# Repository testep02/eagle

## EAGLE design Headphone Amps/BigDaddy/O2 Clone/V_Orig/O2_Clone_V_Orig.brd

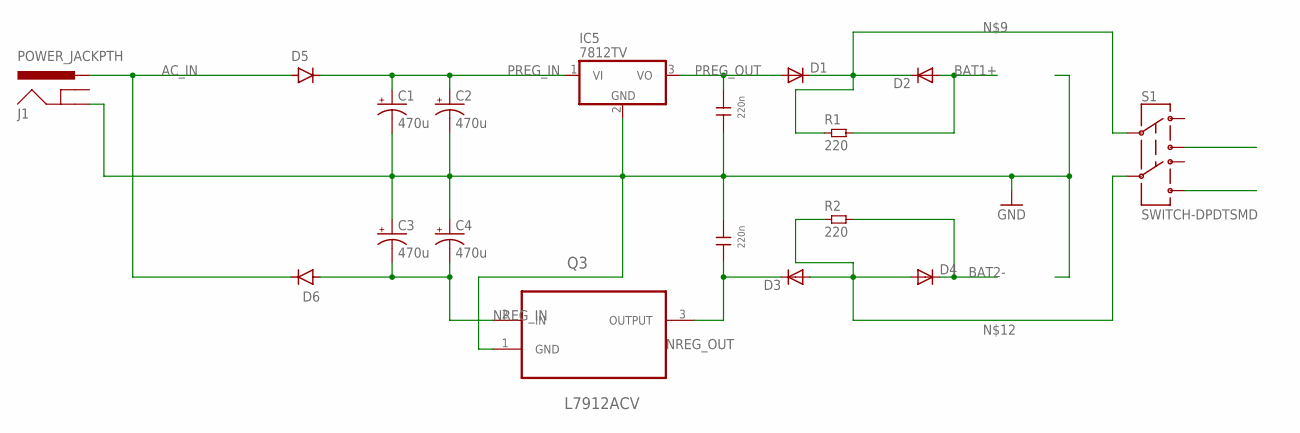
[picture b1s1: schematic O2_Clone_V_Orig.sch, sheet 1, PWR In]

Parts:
C1, C2, C3, C4: 470u; E5-10,5
C5, C6: 220n; 3,0X7,5RM5,0
D1, D2, D3, D4: DIODE-SMB; SMB
D5, D6: DIODE-SMX; SMX
IC5: 7812TV; TO220V
J1: POWER_JACKPTH; POWER_JACK_PTH
Q3: L7912ACV; TO254P450X1020X1935-3P
R1, R2: 220; 0603L3
S1: SWITCH-DPDTSMD; AYZ0202

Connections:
AC_IN: D5.1 (ANODE), D6.2 (CATHODE), J1.PWR
BAT1+: D2.A, R1.P$2 (2)
BAT2-: D4.C, R2.P$2 (2)
GND: C1.-, C2.-, C3.+, C4.+, C5.1, C6.2, IC5.2 (GND), J1.GND, Q3.1 (GND); also elsewhere on the board
unnamed: D1.C, D2.C, R1.P$1 (1), S1.2
unnamed: D3.A, D4.A, R2.P$1 (1), S1.5
NEG_OUT: S1.6
NREG_IN: C3.-, C4.-, D6.1 (ANODE), Q3.2 (IN)
NREG_OUT: C6.1, D3.C, Q3.3 (OUTPUT)
POS_OUT: S1.3
PREG_IN: C1.+, C2.+, D5.2 (CATHODE), IC5.1 (VI)
PREG_OUT: C5.2, D1.A, IC5.3 (VO)

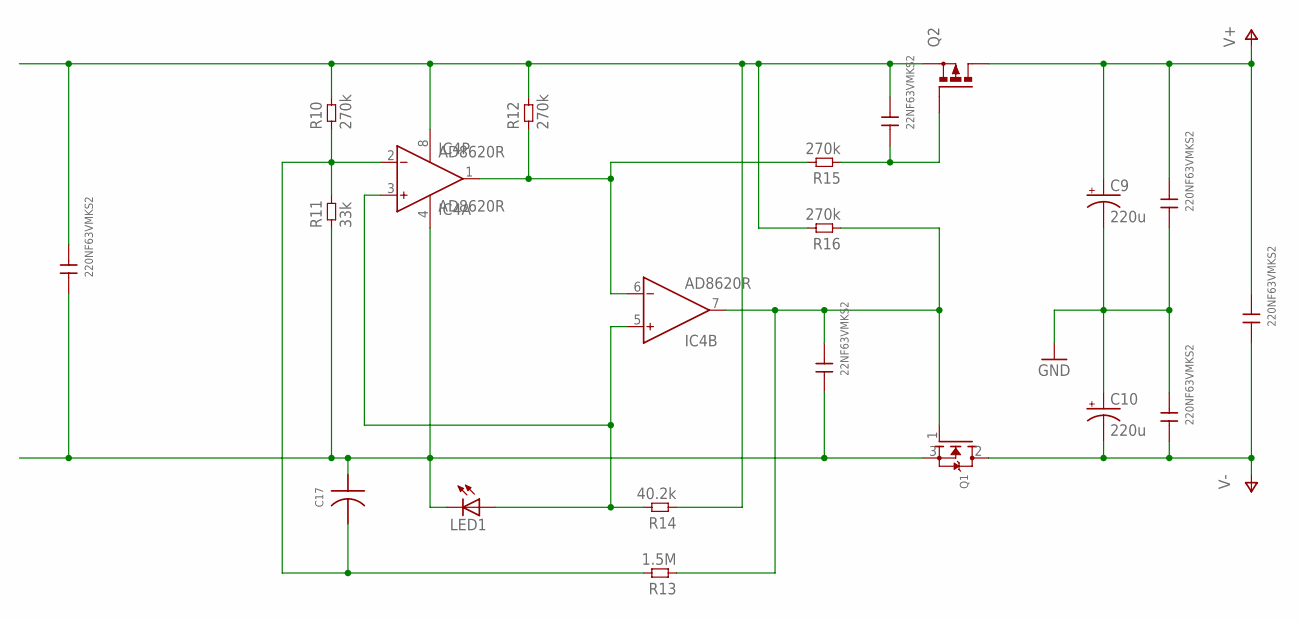
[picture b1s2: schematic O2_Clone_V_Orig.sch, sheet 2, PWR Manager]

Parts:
C7, C8: 22NF63VMKS2; 2,5X6,5RM5,0
C9, C10: 220u; E3,5-8
C11, C12, C13, C14: 220NF63VMKS2; 3,0X7,5RM5,0
C17: PCAP0805LEVEL3; R0805
IC4: AD8620R; SO8
LED1: LED3MM
Q1: MOSFET-NGDS_TO220V; TO220V
Q2: PMOSFET_PTO220BV; TO220BV
R10, R12, R15, R16: 270k; 0603L3
R11: 33k; 0603L3
R13: 1.5M; 0603L3
R14: 40.2k; 0603L3

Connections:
GND: C9.-, C10.+, C11.1, C12.2; also elsewhere on the board
unnamed: IC4.1 (OUT), IC4.6 (IN-), R12.P$1 (1), R15.P$2 (2)
unnamed: IC4.3 (IN+), IC4.5 (IN+), LED1.A, R14.P$2 (2)
unnamed: C8.1, C14.1, C17.P$2, IC4.4 (V-), LED1.K (C), Q1.3 (S), R11.P$1 (1)
unnamed: C17.P$1, IC4.2 (IN-), R10.P$1 (1), R11.P$2 (2), R13.P$2 (2)
unnamed: C7.2, C14.2, IC4.8 (V+), Q2.S, R10.P$2 (2), R12.P$2 (2), R14.P$1 (1), R16.P$2 (2)
unnamed: C7.1, Q2.G, R15.P$1 (1)
unnamed: C8.2, IC4.7 (OUT), Q1.1 (G), R13.P$1 (1), R16.P$1 (1)
V+: C9.+, C11.2, C13.2, Q2.D; also elsewhere on the board
V-: C10.-, C12.1, C13.1, Q1.2 (D); also elsewhere on the board

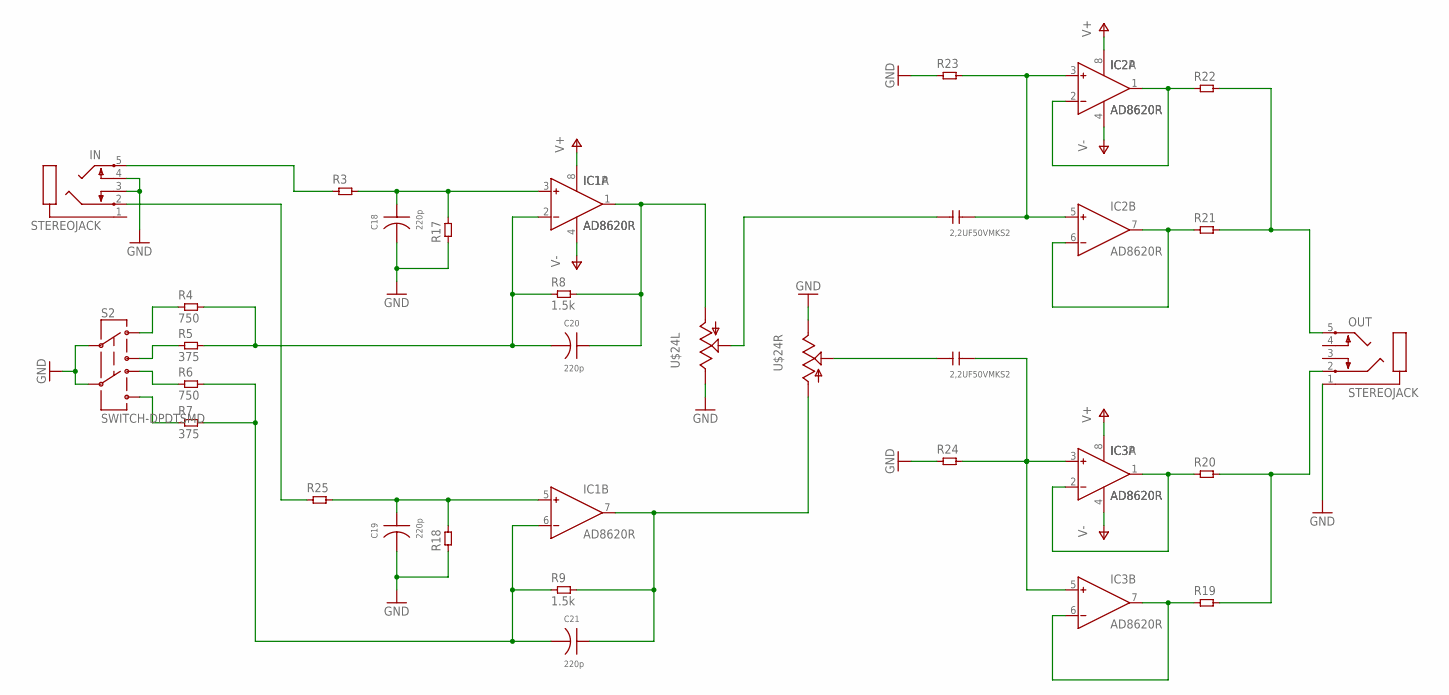
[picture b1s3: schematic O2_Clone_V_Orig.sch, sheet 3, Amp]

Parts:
C15, C16: 2,2UF50VMKS2; 7,2X13,0RM5,0
C18, C19, C20, C21: 220p; R0603
IC1, IC2, IC3: AD8620R; SO8
IN: STEREOJACK; STX3100
OUT: STEREOJACK; STX3100
R3, R17, R18, R19, R20, R21, R22, R23, R24, R25: RES0603L3; 0603L3
R4, R6: 750; 0603L3
R5, R7: 375; 0603L3
R8, R9: 1.5k; 0603L3
S2: SWITCH-DPDTSMD; AYZ0202
U$24: ALPS_RK0971221Z0N; ALPS_RK0971221Z0X

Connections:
GND: C18.P$1, C19.P$1, IN.3, IN.4, OUT.1, R17.P$1 (1), R18.P$1 (1), R23.P$1 (1), R24.P$1 (1), S2.2, S2.5, U$24.I1 (3), U$24.I2 (3); also elsewhere on the board
unnamed: IC2.1 (OUT), IC2.2 (IN-), R22.P$1 (1)
unnamed: IC2.6 (IN-), IC2.7 (OUT), R21.P$1 (1)
unnamed: IC3.1 (OUT), IC3.2 (IN-), R20.P$1 (1)
unnamed: IC3.6 (IN-), IC3.7 (OUT), R19.P$1 (1)
unnamed: OUT.5, R21.P$2 (2), R22.P$2 (2)
unnamed: OUT.2, R19.P$2 (2), R20.P$2 (2)
unnamed: C16.2, IC2.3 (IN+), IC2.5 (IN+), R23.P$2 (2)
unnamed: C15.2, IC3.3 (IN+), IC3.5 (IN+), R24.P$2 (2)
unnamed: C20.P$2, IC1.1 (OUT), R8.P$2 (2), U$24.G1 (1)
unnamed: C20.P$1, IC1.2 (IN-), R4.P$2 (2), R5.P$2 (2), R8.P$1 (1)
unnamed: C21.P$2, IC1.7 (OUT), R9.P$2 (2), U$24.G2 (1)
unnamed: C15.1, U$24.O2 (2)
unnamed: C18.P$2, IC1.3 (IN+), R3.P$2 (2), R17.P$2 (2)
unnamed: C19.P$2, IC1.5 (IN+), R18.P$2 (2), R25.P$2 (2)
unnamed: IN.5, R3.P$1 (1)
unnamed: IN.2, R25.P$1 (1)
unnamed: R5.P$1 (1), S2.3
unnamed: R6.P$1 (1), S2.4
unnamed: R4.P$1 (1), S2.1
unnamed: R7.P$1 (1), S2.6
unnamed: C21.P$1, IC1.6 (IN-), R6.P$2 (2), R7.P$2 (2), R9.P$1 (1)
unnamed: C16.1, U$24.O1 (2)
S1: U$24.S1
S2: U$24.S2
V+: IC1.8 (V+), IC2.8 (V+), IC3.8 (V+); also elsewhere on the board
V-: IC1.4 (V-), IC2.4 (V-), IC3.4 (V-); also elsewhere on the board

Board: 2 copper layers, 67 parts (0 on the bottom side), 41 nets, no tracks yet.

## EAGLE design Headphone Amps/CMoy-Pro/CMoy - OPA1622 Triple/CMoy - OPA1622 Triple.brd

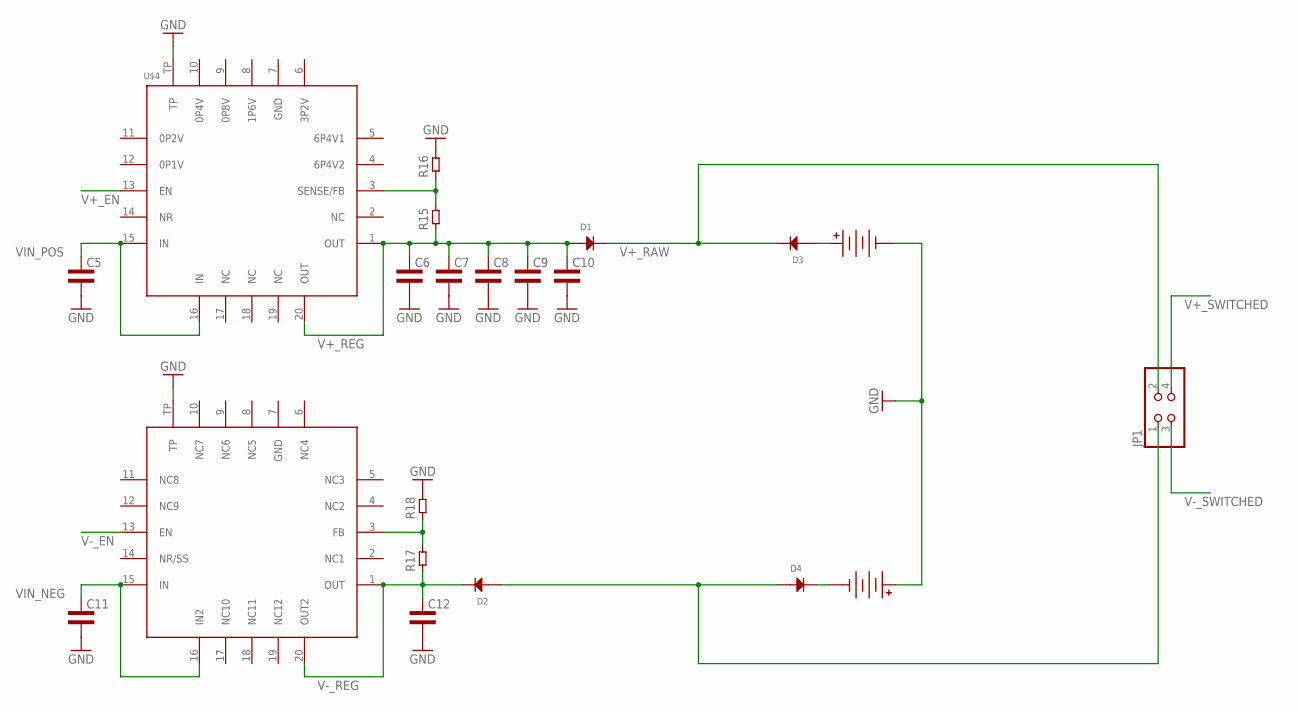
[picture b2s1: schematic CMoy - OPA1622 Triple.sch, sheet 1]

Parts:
BATT1, BATT2: BATT_9V; 9V_FEMALE
C5, C6, C7, C8, C9, C10, C11, C12: CAP0805L3; 0805L3
D1, D2, D3, D4: DIODEMINI2-F3-B; MINI2-F3-B
JP1: PINHD-2X2; 2X02
R15, R16, R17, R18: RES0603L3; 0603L3
U$4: POWER-SUPPLY_POS_V1_TI_LDO_TPS7A4700; POWER-SUPPLY_POS_V1_TI_LDO_VQFN-20
U$5: POWER-SUPPLY_POS_V1_TI_LDO_TPS7A3301RGWT; POWER-SUPPLY_POS_V1_TI_LDO_VQFN-20

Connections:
GND: BATT1.N1 (NEG), BATT1.N2 (NEG), BATT1.N3 (NEG), BATT2.P1 (POS), BATT2.P2 (POS), BATT2.P3 (POS), C5.2, C6.2, C7.2, C8.2, C9.2, C10.2, C11.2, C12.2, R16.P$2 (2), R18.P$2 (2), U$4.TP, U$5.TP; also elsewhere on the board
unnamed: BATT1.P1 (POS), BATT1.P2 (POS), BATT1.P3 (POS), D3.2 (ANODE)
unnamed: BATT2.N1 (NEG), BATT2.N2 (NEG), BATT2.N3 (NEG), D4.1 (CATHODE)
V+_EN: U$4.13 (EN)
V+_FB: R15.P$2 (2), R16.P$1 (1), U$4.3 (SENSE/FB)
V+_RAW: D1.1 (CATHODE), D3.1 (CATHODE), JP1.2
V+_REG: C6.1, C7.1, C8.1, C9.1, C10.1, D1.2 (ANODE), R15.P$1 (1), U$4.1 (OUT), U$4.20 (OUT)
V+_SWITCHED: JP1.4; also elsewhere on the board
V-_EN: U$5.13 (EN)
V-_FB: R17.P$2 (2), R18.P$1 (1), U$5.3 (FB)
V-_RAW: D2.2 (ANODE), D4.2 (ANODE), JP1.1
V-_REG: C12.1, D2.1 (CATHODE), R17.P$1 (1), U$5.1 (OUT), U$5.20 (OUT2)
V-_SWITCHED: JP1.3; also elsewhere on the board
VIN_NEG: C11.1, U$5.15 (IN), U$5.16 (IN2)
VIN_POS: C5.1, U$4.15 (IN), U$4.16 (IN)

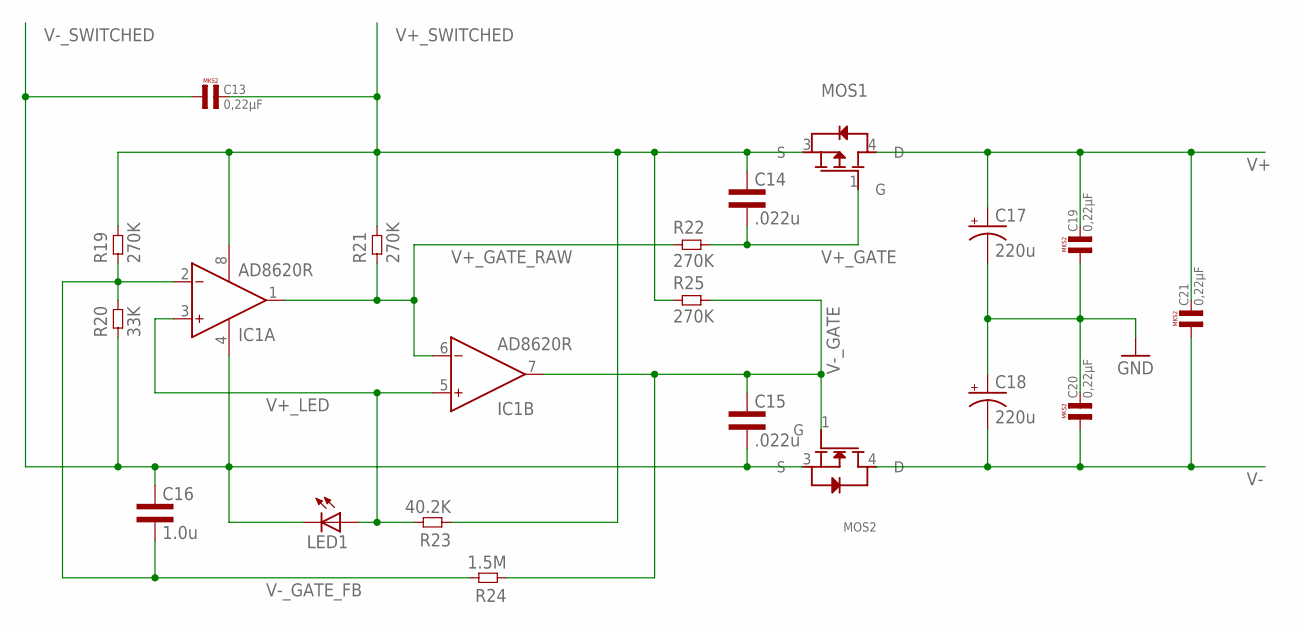
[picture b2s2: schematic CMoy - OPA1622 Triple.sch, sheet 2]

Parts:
C13, C19, C20, C21: 0,22µF; R5B3
C14, C15: .022u; 0603L3
C16: 1.0u; 0603L3
C17, C18: 220u; E3,5-8
IC1: AD8620R; SO8
LED1: LED3MM
MOS1: MOSFET-P; DPAK-3
MOS2: MOSFET-N; DPAK-3
R19, R21, R22, R25: 270K; 0603L3
R20: 33K; 0603L3
R23: 40.2K; 0603L3
R24: 1.5M; 0603L3

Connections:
GND: C17.-, C18.+, C19.1, C20.2; also elsewhere on the board
V+: C17.+, C19.2, C21.2, MOS1.4 (D); also elsewhere on the board
V+_GATE: C14.P$2 (2), MOS1.1 (G), R22.P$2 (2)
V+_GATE_RAW: IC1.1 (OUT), IC1.6 (IN-), R21.P$1 (1), R22.P$1 (1)
V+_LED: IC1.3 (IN+), IC1.5 (IN+), LED1.A, R23.P$2 (2)
V+_SWITCHED: C13.2, C14.P$1 (1), IC1.8 (V+), MOS1.3 (S), R19.P$2 (2), R21.P$2 (2), R23.P$1 (1), R25.P$1 (1); also elsewhere on the board
V-: C18.-, C20.1, C21.1, MOS2.4 (D); also elsewhere on the board
V-_GATE: C15.P$1 (1), IC1.7 (OUT), MOS2.1 (G), R24.P$1 (1), R25.P$2 (2)
V-_GATE_FB: C16.P$2 (2), IC1.2 (IN-), R19.P$1 (1), R20.P$2 (2), R24.P$2 (2)
V-_SWITCHED: C13.1, C15.P$2 (2), C16.P$1 (1), IC1.4 (V-), LED1.K (C), MOS2.3 (S), R20.P$1 (1); also elsewhere on the board

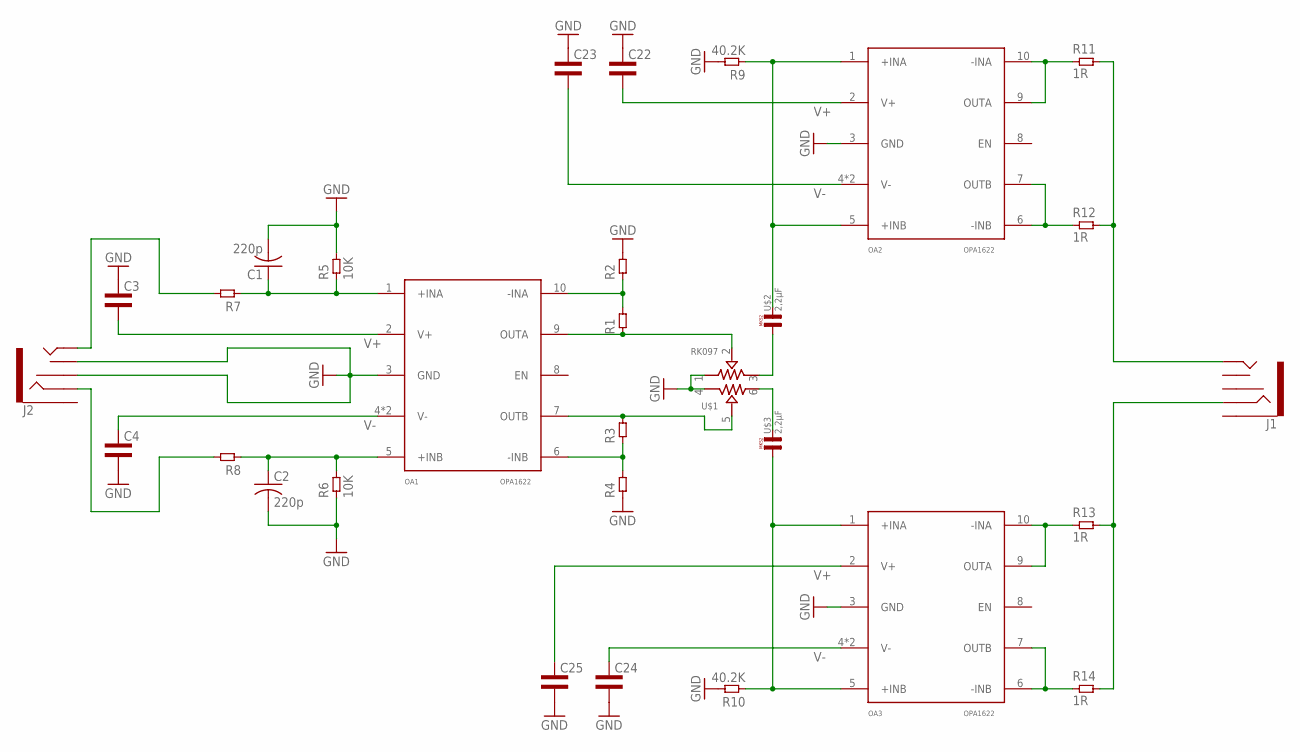
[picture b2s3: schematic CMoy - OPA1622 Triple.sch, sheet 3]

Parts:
C1, C2: 220p; C025-050X050
C3, C4, C22, C23, C24, C25: CAP0603L3; 0603L3
J1, J2: AUDIO-JACK2SMD; AUDIO-JACK-3.5MM-SMD
OA1, OA2, OA3: OPA1622; S-PVSON-N10
R1, R2, R3, R4, R7, R8: RES0603L3; 0603L3
R5, R6: 10K; 0603L3
R9, R10: 40.2K; 0603L3
R11, R12, R13, R14: 1R; 0805L3
U$1: RK097
U$2, U$3: 2,2µF; R5B7K2

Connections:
GND: C1.2, C2.2, C3.P$1 (1), C4.P$2 (2), C22.P$1 (1), C23.P$1 (1), C24.P$2 (2), C25.P$2 (2), J2.RSH, J2.TSH, OA1.3 (GND), OA2.3 (GND), OA3.3 (GND), R2.P$2 (2), R4.P$1 (1), R5.P$2 (2), R6.P$1 (1), R9.P$2 (2), R10.P$2 (2), U$1.1, U$1.4; also elsewhere on the board
unnamed: C1.1, OA1.1 (+INA), R5.P$1 (1), R7.P$1 (1)
unnamed: C2.1, OA1.5 (+INB), R6.P$2 (2), R8.P$1 (1)
unnamed: OA1.10 (-INA), R1.P$2 (2), R2.P$1 (1)
unnamed: OA1.6 (-INB), R3.P$1 (1), R4.P$2 (2)
unnamed: OA1.9 (OUTA), R1.P$1 (1), U$1.2
unnamed: OA1.7 (OUTB), R3.P$2 (2), U$1.5
unnamed: U$1.3, U$2.1
unnamed: J2.TIP, R7.P$2 (2)
unnamed: J2.RING, R8.P$2 (2)
unnamed: U$1.6, U$3.2
unnamed: OA2.1 (+INA), OA2.5 (+INB), R9.P$1 (1), U$2.2
unnamed: OA3.1 (+INA), OA3.5 (+INB), R10.P$1 (1), U$3.1
unnamed: OA2.9 (OUTA), OA2.10 (-INA), R11.1
unnamed: OA3.9 (OUTA), OA3.10 (-INA), R13.1
unnamed: OA3.6 (-INB), OA3.7 (OUTB), R14.1
unnamed: OA2.6 (-INB), OA2.7 (OUTB), R12.1
unnamed: J1.TIP, R11.2, R12.2
unnamed: J1.RING, R13.2, R14.2
V+: C3.P$2 (2), C22.P$2 (2), C25.P$1 (1), OA1.2 (V+), OA2.2 (V+), OA3.2 (V+); also elsewhere on the board
V-: C4.P$1 (1), C23.P$2 (2), C24.P$1 (1), OA1.4 (V-), OA1.TP (V-), OA2.4 (V-), OA2.TP (V-), OA3.4 (V-), OA3.TP (V-); also elsewhere on the board

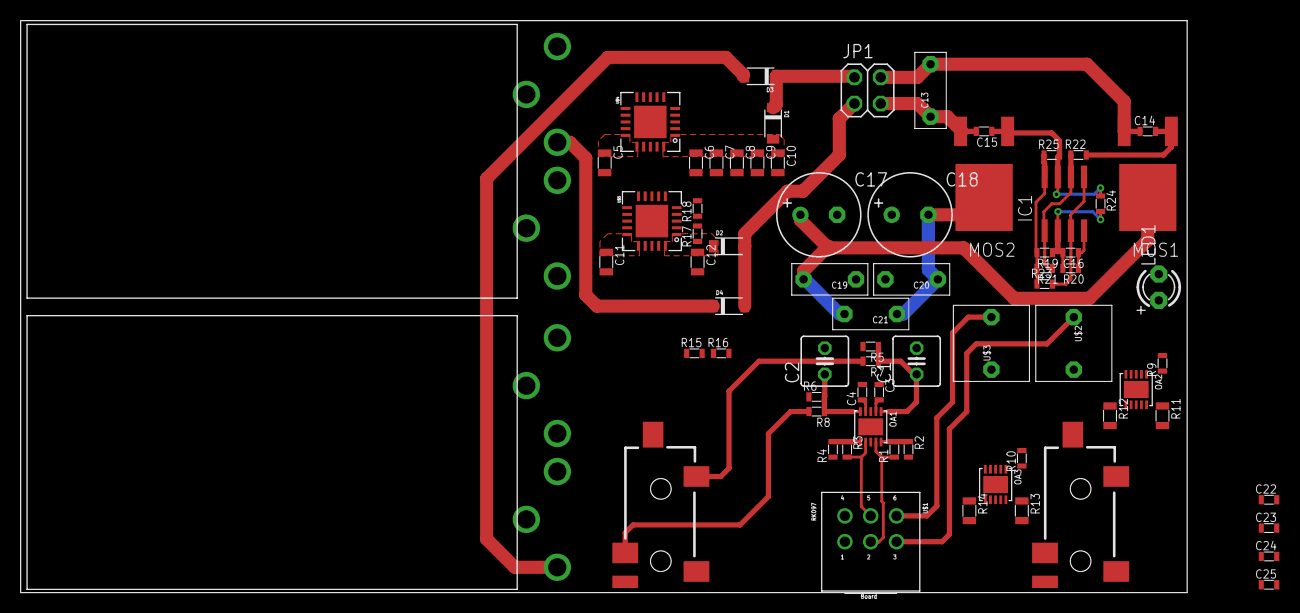
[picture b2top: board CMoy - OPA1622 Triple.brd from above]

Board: 2 copper layers, 112.9 x 55.4 mm, 71 parts (0 on the bottom side), 38 nets.

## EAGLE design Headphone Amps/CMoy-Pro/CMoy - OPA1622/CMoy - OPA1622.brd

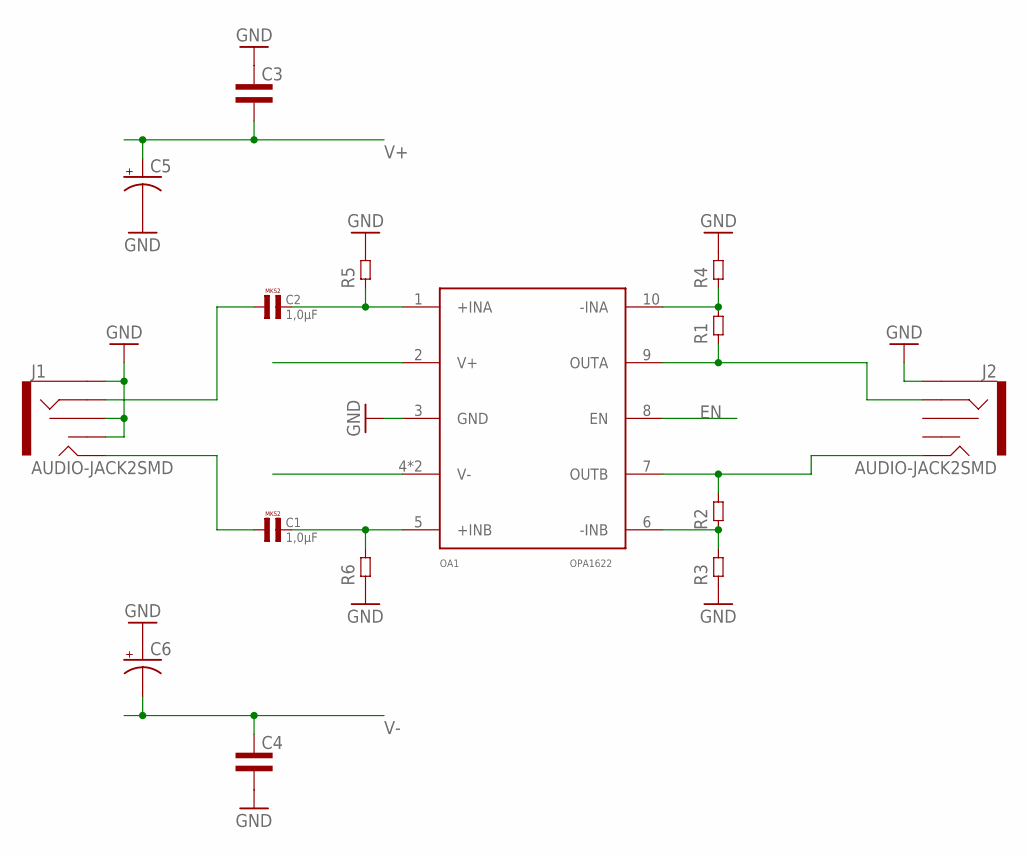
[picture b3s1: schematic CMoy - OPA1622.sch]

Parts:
C1, C2: 1,0µF; R5B5
C3, C4: CAP0402L3; 0402L3
C5, C6: CPOL-USE5-10.5; E5-10,5
J1, J2: AUDIO-JACK2SMD; AUDIO-JACK-3.5MM-SMD
OA1: OPA1622; S-PVSON-N10
R1, R2, R3, R4, R5, R6: RES0402L3; 0402L3

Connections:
EN: OA1.8 (EN)
GND: C3.P$1 (1), C4.P$2 (2), C5.-, C6.+, J1.RSH, J1.SLEEVE, J1.TSH, J2.SLEEVE, OA1.3 (GND), R3.P$1 (1), R4.P$2 (2), R5.P$2 (2), R6.P$1 (1)
unnamed: C1.2, OA1.5 (+INB), R6.P$2 (2)
unnamed: C2.2, OA1.1 (+INA), R5.P$1 (1)
unnamed: OA1.10 (-INA), R1.P$2 (2), R4.P$1 (1)
unnamed: OA1.6 (-INB), R2.P$1 (1), R3.P$2 (2)
unnamed: J2.TIP, OA1.7 (OUTB), R2.P$2 (2)
unnamed: J2.RING, OA1.9 (OUTA), R1.P$1 (1)
unnamed: C1.1, J1.TIP
unnamed: C2.1, J1.RING
V+: C3.P$2 (2), C5.+, OA1.2 (V+)
V-: C4.P$1 (1), C6.-, OA1.4 (V-), OA1.TP (V-)

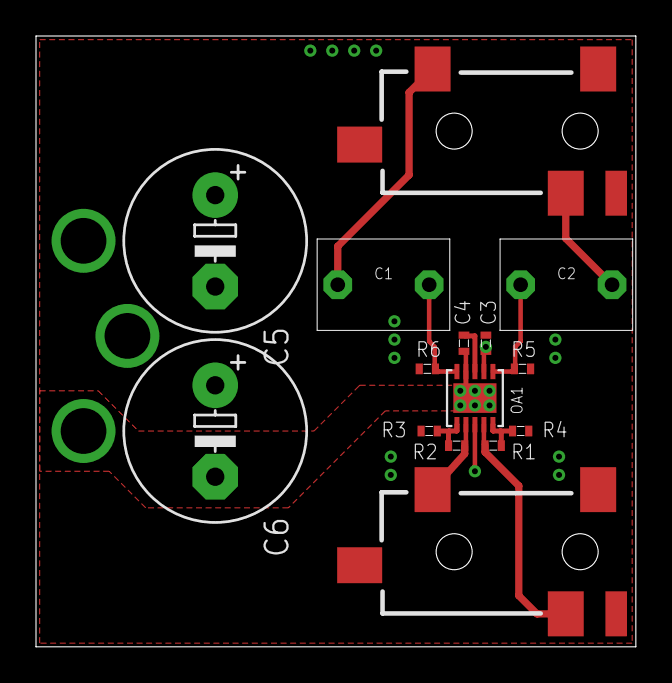
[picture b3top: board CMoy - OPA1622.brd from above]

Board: 2 copper layers, 33.3 x 33.9 mm, 15 parts (0 on the bottom side), 11 nets.

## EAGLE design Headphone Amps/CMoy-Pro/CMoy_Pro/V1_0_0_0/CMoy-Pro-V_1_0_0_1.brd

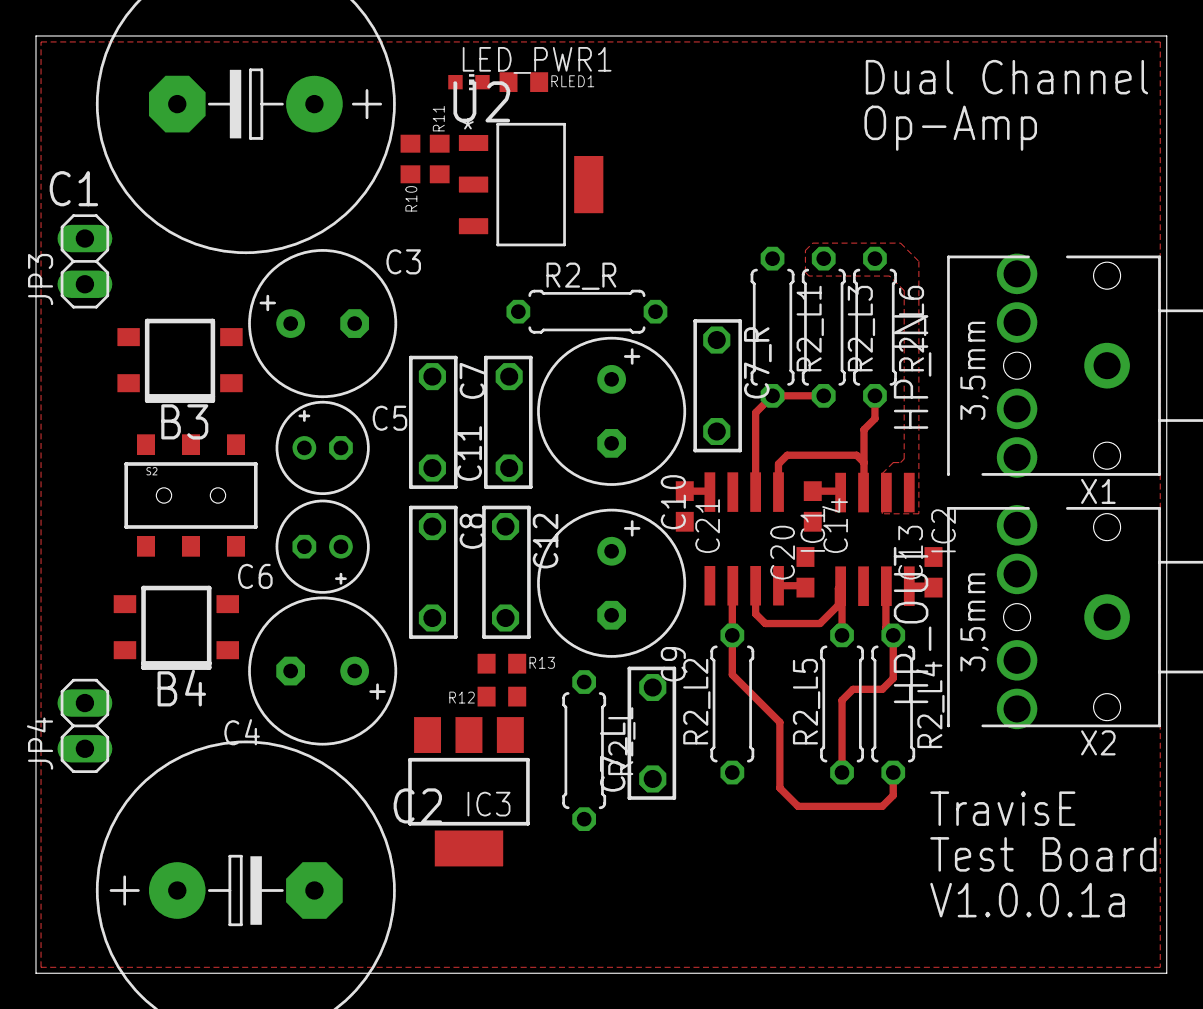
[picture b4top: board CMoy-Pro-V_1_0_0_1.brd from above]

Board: 2 copper layers, 62.8 x 52.1 mm, 43 parts (0 on the bottom side), 24 nets.

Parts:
B3, B4: RECTIFIER-S40; TO-269AA
C1, C2: 4700u; E7,5-16
C3, C4, C9, C10: 470u; E3,5-8
C5, C6: 10u; E2-5
C7, C8, C11, C12: 1,0NF100VMKS22; 2,5X5,5RM5,0
C7_L, C7_R: 1uF; 2,5X5,5RM5,0
C13, C14, C20, C21: 100n; C0603
IC1, IC2: AD8620R; SO8
IC3: LM337IMP; SOT-223
JP3, JP4: 1X02
LED_PWR1: CHIP-LED0603
R2_L, R2_L1, R2_L2, R2_L3, R2_L4, R2_R: 10K; 0207/7
R2_L5, R2_L6: 10; 0207/7
R10, R12: 200; R0603
R11, R13: 2200; R0603
RLED1: 10K; R0603
S2: SWITCH-DPDTSMD; AYZ0202
U2: LM317MDCY; SOT230P700X180-4N
X1, X2: STEREOJACK; STX3100

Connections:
GND: B3.-, B4.+, C1.-, C2.+, C3.-, C4.+, C5.-, C6.+, C7.1, C8.1, C9.-, C10.+, C11.1, C12.1, C13.2, C14.2, C20.2, C21.2, R2_L.2, R2_L1.1, R2_L2.1, R2_R.1, R11.1, R13.1, RLED1.2, X1.1, X2.1
IN_R: C7_R.2, IC1.3, R2_R.2
unnamed: C7_L.2, IC1.5, R2_L.1
unnamed: LED_PWR1.C, RLED1.1
unnamed: IC3.1, R12.1, R13.2
unnamed: C7_L.1, X1.2
unnamed: IC2.1, IC2.2, R2_L3.1, R2_L6.1, X2.4, X2.5
unnamed: IC1.2, R2_L1.2, R2_L3.2
unnamed: C7_R.1, X1.5
unnamed: B3.+, S2.2
unnamed: R10.1, R11.2, U2.1
unnamed: B4.-, S2.5
unnamed: IC1.6, R2_L2.2, R2_L4.2
unnamed: B4.AC1, JP4.1
unnamed: B3.AC2, JP3.2
unnamed: C1.+, C3.+, C5.+, C7.2, S2.3, U2.3
unnamed: B3.AC1, JP3.1
unnamed: B4.AC2, JP4.2
unnamed: C2.-, C4.-, C6.-, C8.2, IC3.2, IC3.4, S2.6
unnamed: IC1.1, IC2.3, R2_L6.2
unnamed: IC1.7, IC2.5, R2_L5.2
unnamed: IC2.6, IC2.7, R2_L4.1, R2_L5.1, X2.2, X2.3
V+: C9.+, C11.2, C13.1, C20.1, IC1.8, IC2.8, LED_PWR1.A, R10.2, U2.2, U2.4
V-: C10.-, C12.2, C14.1, C21.1, IC1.4, IC2.4, IC3.3, R12.2

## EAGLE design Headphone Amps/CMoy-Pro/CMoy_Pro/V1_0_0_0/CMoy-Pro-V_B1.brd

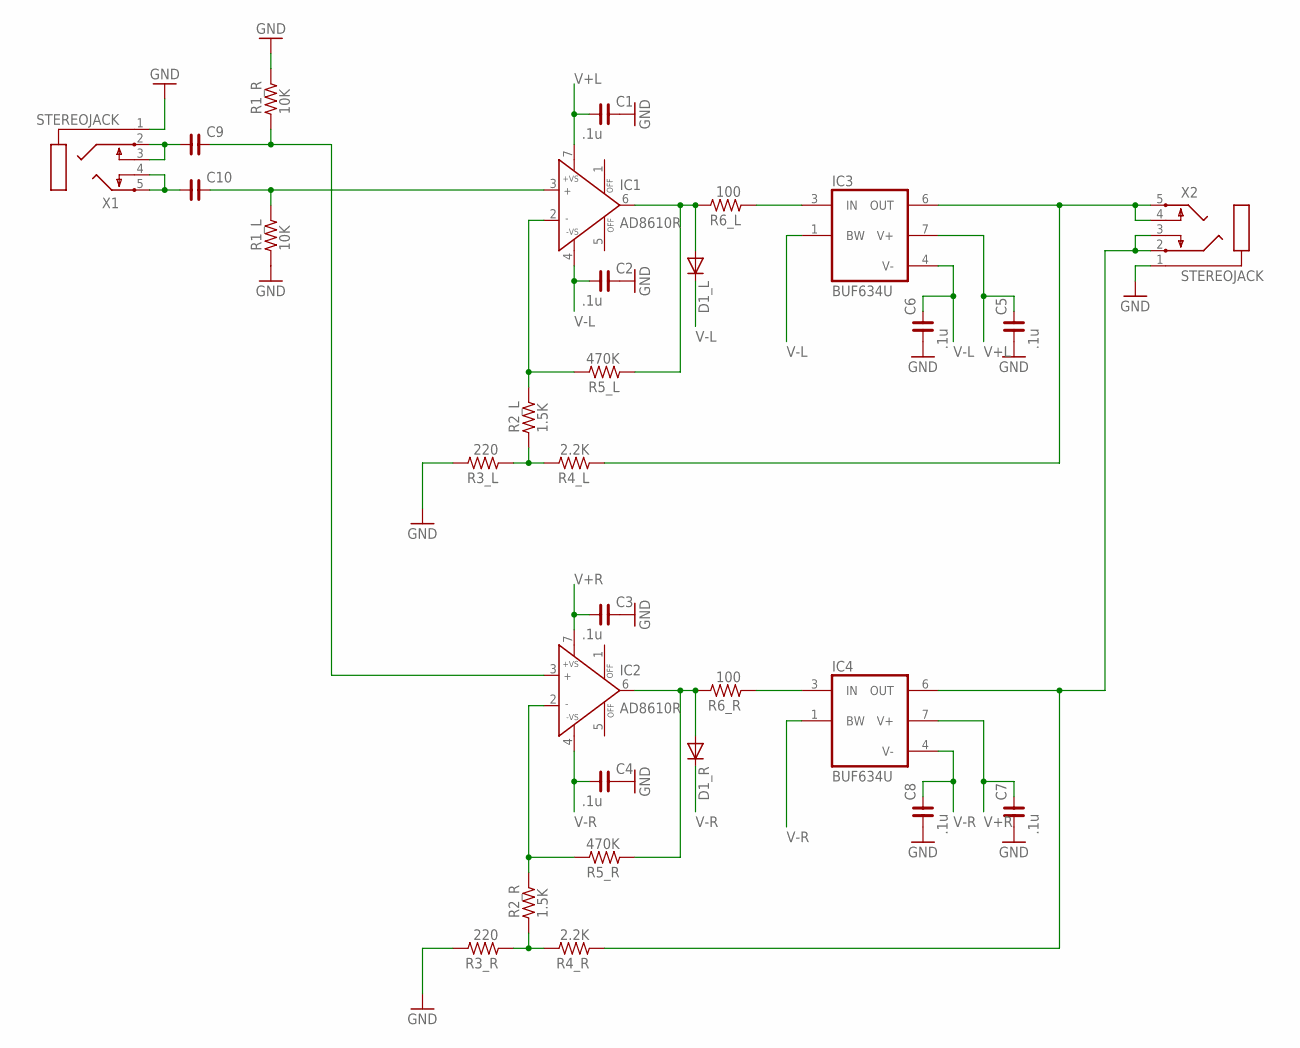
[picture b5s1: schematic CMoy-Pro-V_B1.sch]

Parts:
C1, C2, C3, C4, C5, C6, C7, C8: .1u; C0603
C9, C10: C_1210; C1210
D1_L, D1_R: DIODE-SOD-123; SOD-123
IC1, IC2: AD8610R; SO8
IC3, IC4: BUF634U; SO08
R1_L, R1_R: 10K; R0805
R2_L, R2_R: 1.5K; R0805
R3_L, R3_R: 220; R0805
R4_L, R4_R: 2.2K; R0805
R5_L, R5_R: 470K; R0805
R6_L, R6_R: 100; R0805
X1, X2: STEREOJACK; STX3100

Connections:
GND: C1.2, C2.2, C3.2, C4.2, C5.1, C6.1, C7.1, C8.1, R1_L.1, R1_R.2, R3_L.2, R3_R.2, X1.1, X2.1
IN_R: C10.2, IC1.3 (IN+), R1_L.2
unnamed: C9.2, IC2.3 (IN+), R1_R.1
unnamed: IC3.6 (OUT), R4_L.1, X2.4, X2.5
unnamed: IC4.6 (OUT), R4_R.1, X2.2, X2.3
unnamed: C9.1, X1.2, X1.3
unnamed: D1_R.A, IC2.6 (OUT), R5_R.1, R6_R.2
unnamed: IC4.3 (IN), R6_R.1
unnamed: C10.1, X1.4, X1.5
unnamed: D1_L.A, IC1.6 (OUT), R5_L.1, R6_L.2
unnamed: IC3.3 (IN), R6_L.1
unnamed: IC1.2 (IN-), R2_L.2, R5_L.2
unnamed: IC2.2 (IN-), R2_R.2, R5_R.2
unnamed: R2_L.1, R3_L.1, R4_L.2
unnamed: R2_R.1, R3_R.1, R4_R.2
V+L: C1.1, C5.2, IC1.7 (+VS), IC3.7 (V+)
V+R: C3.1, C7.2, IC2.7 (+VS), IC4.7 (V+)
V-L: C2.1, C6.2, D1_L.C, IC1.4 (-VS), IC3.1 (BW), IC3.4 (V-)
V-R: C4.1, C8.2, D1_R.C, IC2.4 (-VS), IC4.1 (BW), IC4.4 (V-)

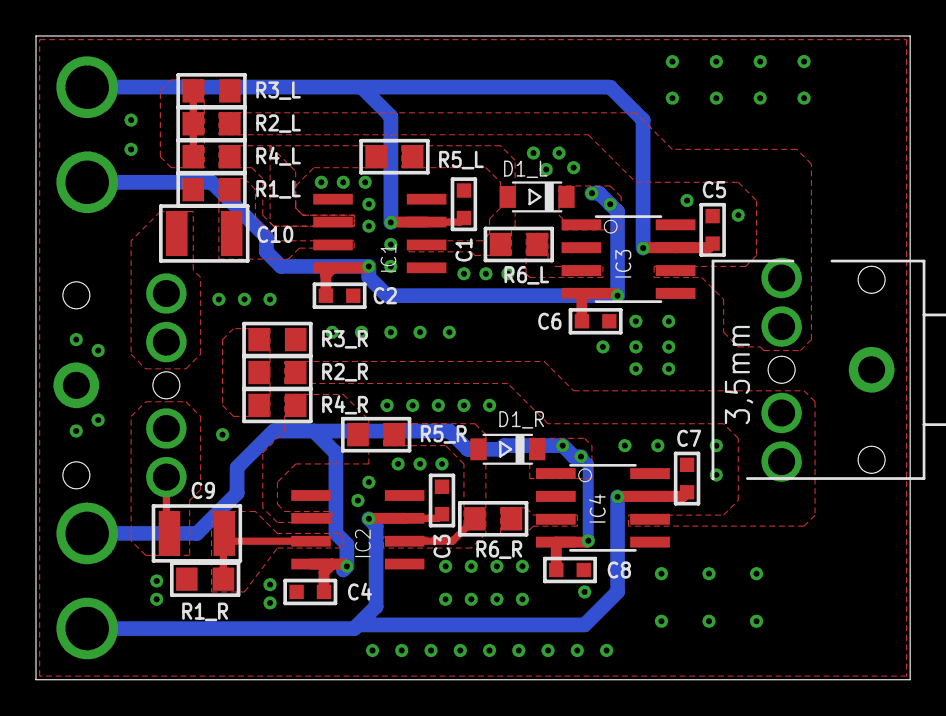
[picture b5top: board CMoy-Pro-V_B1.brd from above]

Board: 2 copper layers, 48.6 x 35.8 mm, 30 parts (1 on the bottom side), 19 nets.

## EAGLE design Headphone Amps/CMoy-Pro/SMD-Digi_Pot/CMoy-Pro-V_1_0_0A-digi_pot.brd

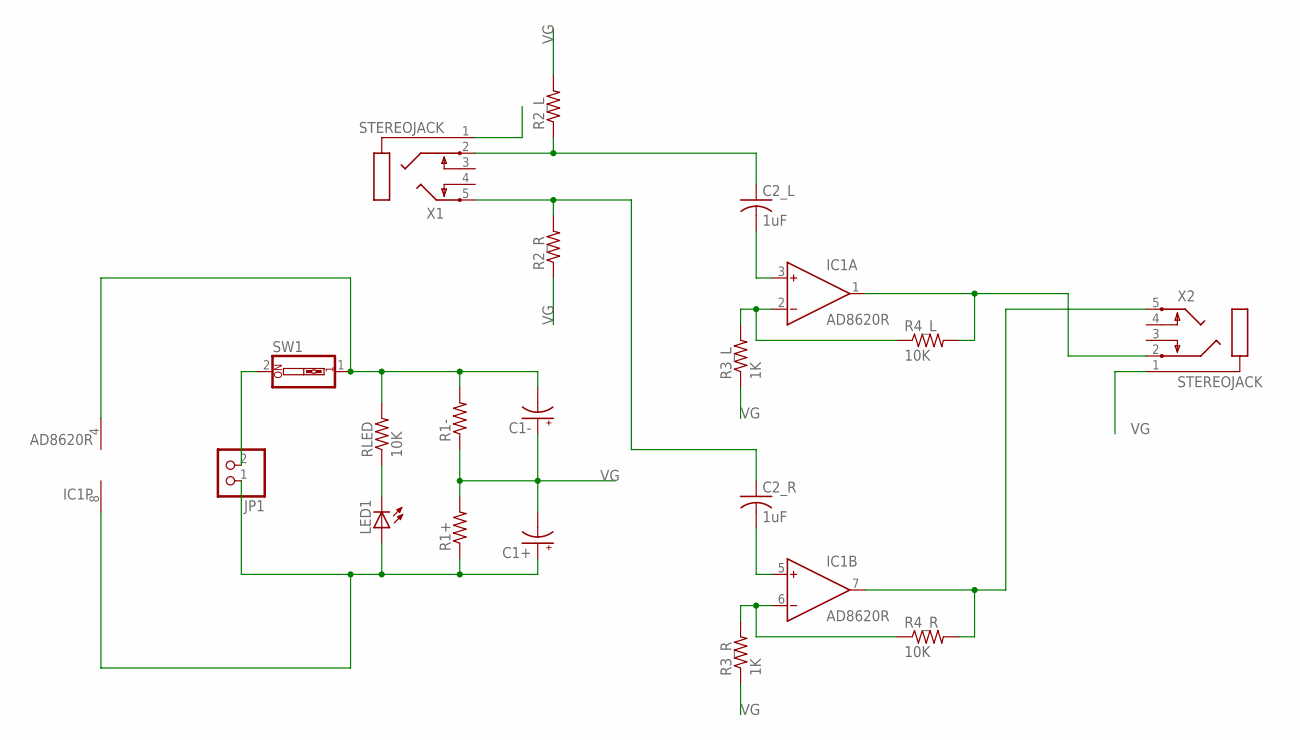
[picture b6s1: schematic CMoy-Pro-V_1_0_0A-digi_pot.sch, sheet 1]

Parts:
C1+, C1-: CPOL-USE2.5-6; E2,5-6
C2_L, C2_R: 1uF; C102-043X133
IC1: AD8620R; SO8
JP1: PINHD-1X2; 1X02
LED1: LEDCHIPLED_0805; CHIPLED_0805
R1+, R1-, R2_L, R2_R: R-US_R0805; R0805
R3_L, R3_R: 1K; R0805
R4_L, R4_R: 10K; R0805
RLED: 10K; R0805
SW1: SW_DIP-1; EDG-01
X1, X2: STEREOJACK; STX3100

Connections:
IN_L: C2_L.1, R2_L.1, X1.2
IN_R: C2_R.1, R2_R.2, X1.5
unnamed: C2_L.2, IC1.3 (IN+)
unnamed: C2_R.2, IC1.5 (IN+)
unnamed: LED1.C, RLED.1
unnamed: IC1.2 (IN-), R3_L.2, R4_L.1
unnamed: IC1.6 (IN-), R3_R.2, R4_R.1
OUT_L: IC1.1 (OUT), R4_L.2, X2.2
OUT_R: IC1.7 (OUT), R4_R.2, X2.5
V+: C1+.+, IC1.8 (V+), JP1.1, LED1.A, R1+.1
V-: JP1.2, SW1.2
V-_ON: C1-.-, IC1.4 (V-), R1-.2, RLED.2, SW1.1
VG: C1+.-, C1-.+, R1+.2, R1-.1, R2_L.2, R2_R.1, R3_L.1, R3_R.1, X1.1, X2.1

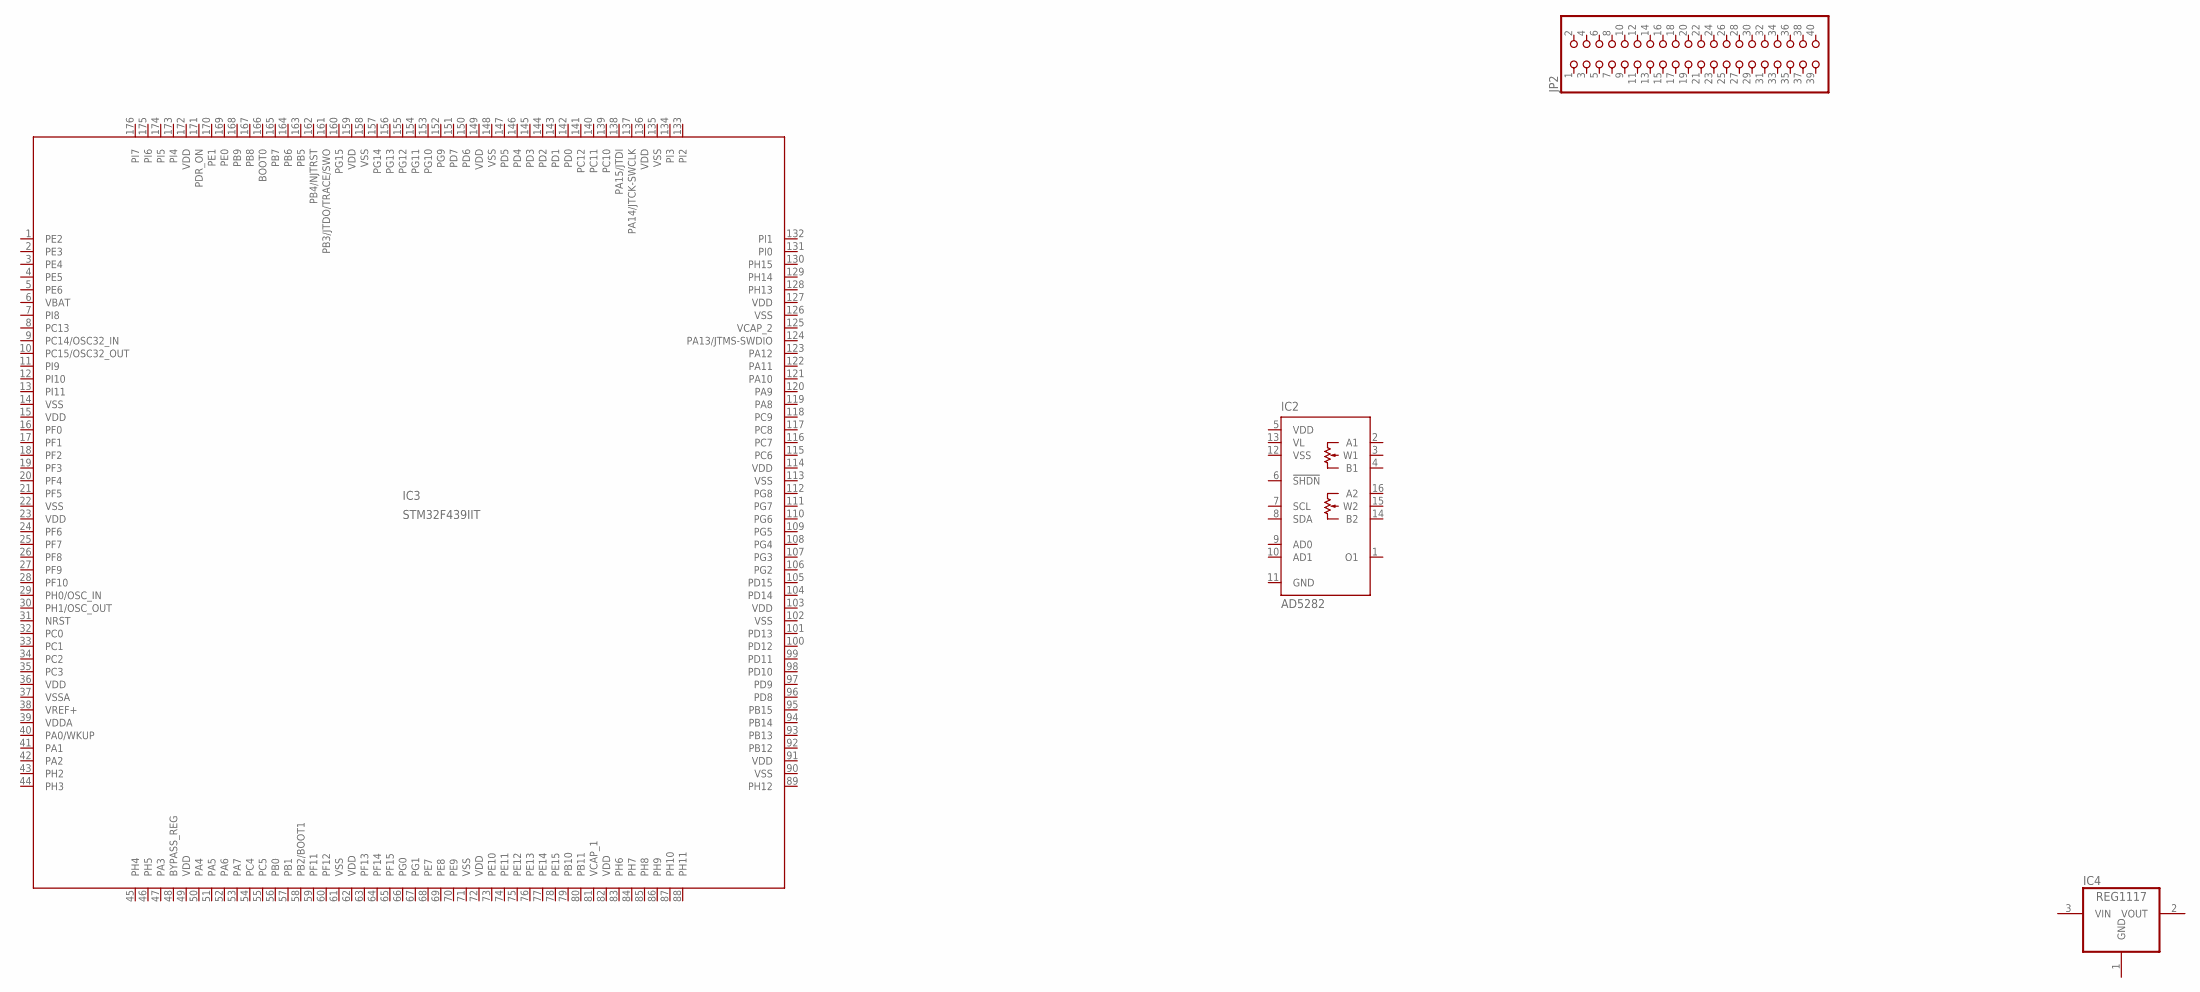
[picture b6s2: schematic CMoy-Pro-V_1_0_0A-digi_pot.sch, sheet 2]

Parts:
IC2: AD5282; TSSOP16
IC3: STM32F439IIT; LQFP-176
IC4: REG1117; SOT223
JP2: PINHD-2X20; 2X20

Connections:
GND: IC2.11 (GND), IC4.1 (GND)
PDR_ON: IC3.171 (PDR_ON)
VBAT: IC3.6 (VBAT)
VCAP_1: IC3.81 (VCAP_1)
VCAP_2: IC3.125 (VCAP_2)
VDD: IC2.5 (VDD), IC3.15 (VDD), IC3.23 (VDD), IC3.36 (VDD), IC3.49 (VDD), IC3.72 (VDD), IC3.82 (VDD), IC3.91 (VDD), IC3.103 (VDD), IC3.114 (VDD), IC3.127 (VDD), IC3.136 (VDD), IC3.149 (VDD), IC3.159 (VDD), IC3.172 (VDD)
VDDA: IC3.39 (VDDA)
VL: IC2.13 (VL)
VREF+: IC3.38 (VREF+)
VSS: IC2.12 (VSS), IC3.14 (VSS), IC3.22 (VSS), IC3.61 (VSS), IC3.71 (VSS), IC3.90 (VSS), IC3.102 (VSS), IC3.113 (VSS), IC3.126 (VSS), IC3.135 (VSS), IC3.148 (VSS), IC3.158 (VSS)
VSSA: IC3.37 (VSSA)

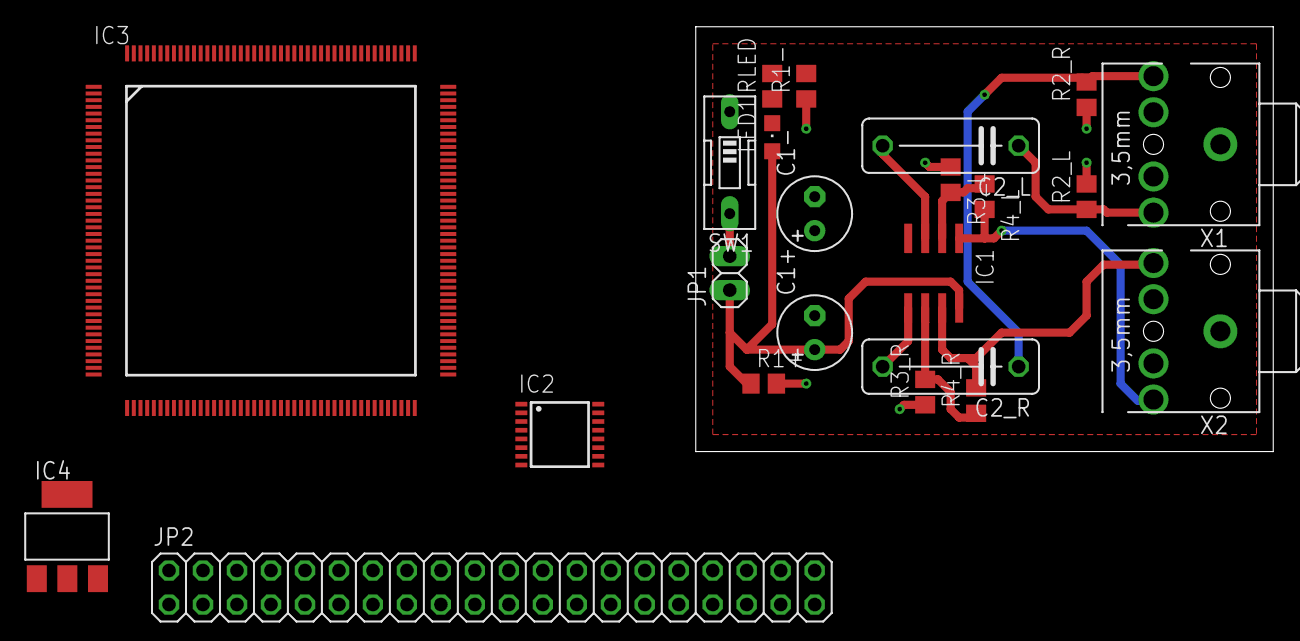
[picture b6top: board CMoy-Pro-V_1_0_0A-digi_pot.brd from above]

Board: 2 copper layers, 43.2 x 31.8 mm, 23 parts (0 on the bottom side), 16 nets.

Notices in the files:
parts and their libraries:
SparkFun-Connectors: Licensing: CC v3.0 Share-Alike You are welcome to use this library for commercial purposes.
rc-master-smd: Copyright (C) 2007, Bob Starr
